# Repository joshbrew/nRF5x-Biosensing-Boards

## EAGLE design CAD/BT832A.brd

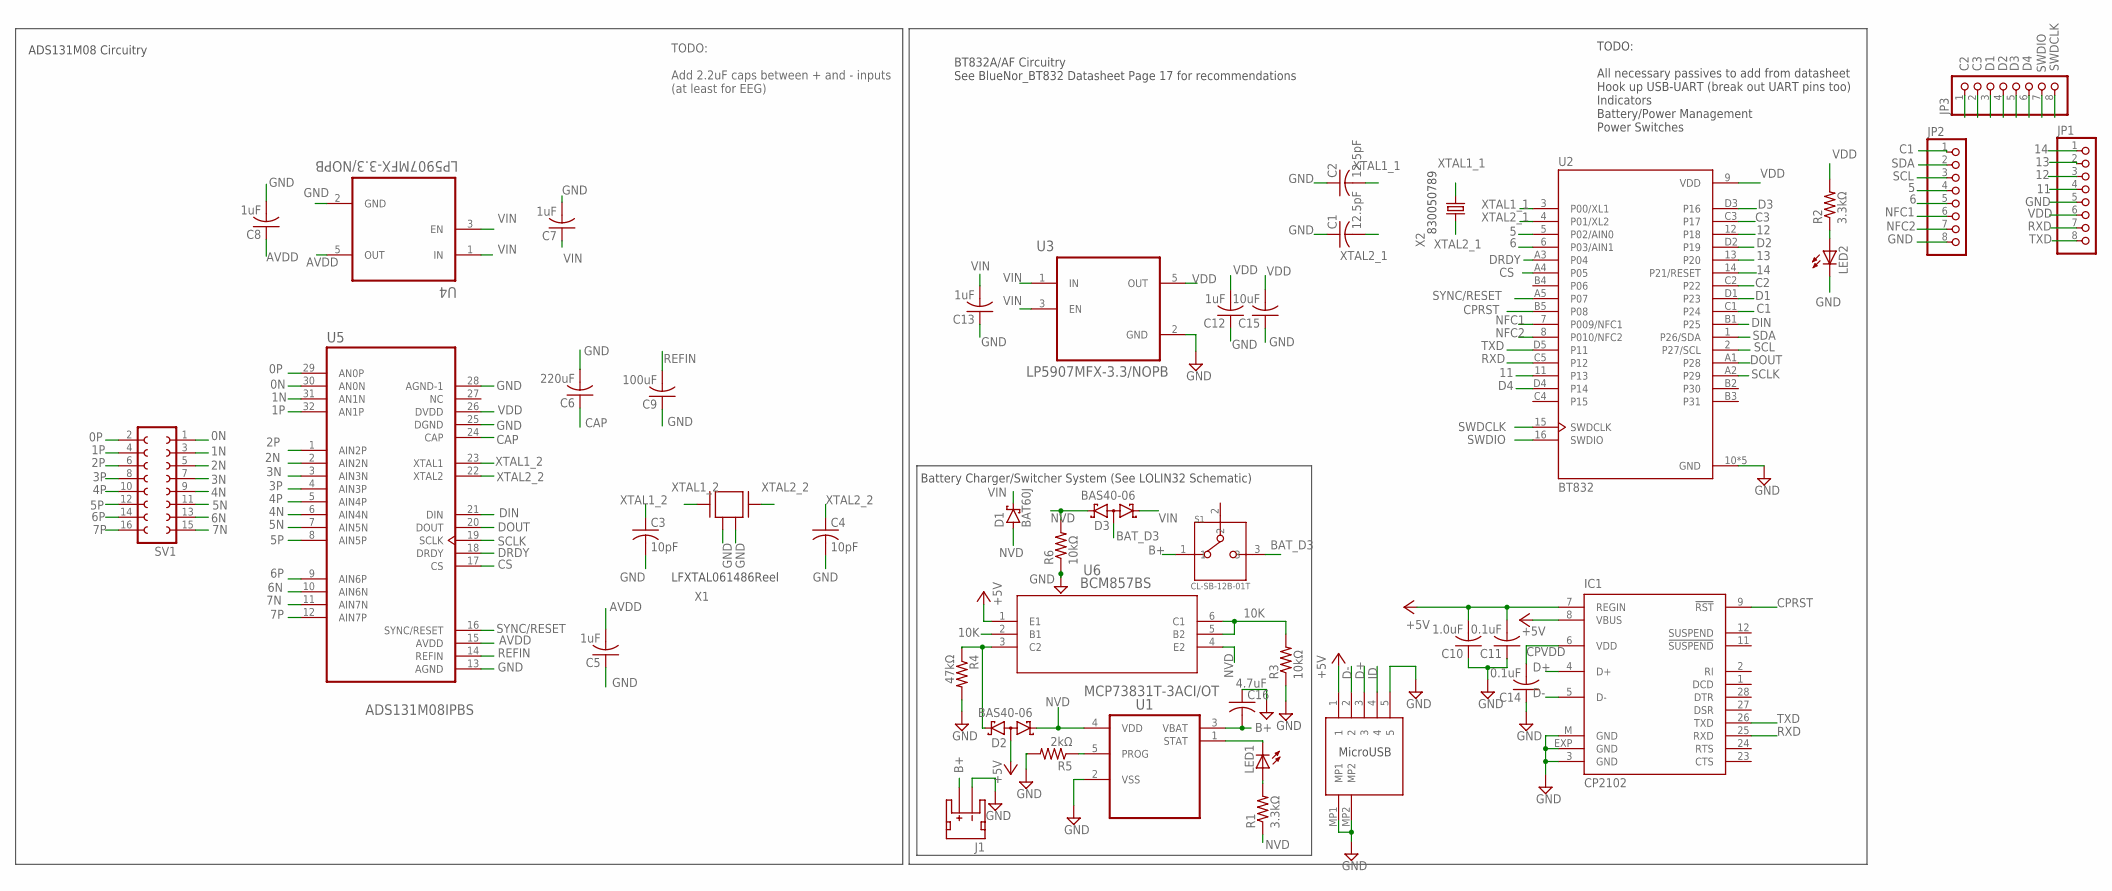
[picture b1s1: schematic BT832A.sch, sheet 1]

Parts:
C1, C2: 12.5pF; C0402
C3, C4: 10pF; C0402
C5, C7, C8, C12, C13: 1uF; C0402
C6: 220uF; C0402
C9: 100uF; C0402
C10: 1.0uF; C0402
C11, C14: 0.1uF; C0402
C15: 10uF; C0402
C16: 4.7uF; C0402
D1: BAT60J; SOD323_ST
D2, D3: BAS40-06; SOT23
IC1: CP2102; MLP28
J1: JST_2MM_MALE; JST-2-SMD
JP1, JP2, JP3: PINHD-1X8CLEANBIG; 1X08-CLEANBIG
LED1, LED2: LEDCHIP-LED0603; CHIP-LED0603
R1, R2: 3.3kΩ; R0402
R3, R6: 10kΩ; R0402
R4: 47kΩ; R0402
R5: 2kΩ; R0402
S1: CL-SB-12B-01T; CL-SB-12B
SV1: FE08-2
U1: MCP73831T-3ACI/OT; SOT95P270X145-5N
U2: BT832; BLEMODULE_BT832
U3, U4: LP5907MFX-3.3/NOPB; SOT95P280X145-5N
U5: ADS131M08IPBS; QFP50P700X700X120-32N
U6: BCM857BS; SOT363_NEX
U$1: DX4R005JJ2R1800
X1: ABM3B-8.000MHZ-B2-T
X2: FC-12M

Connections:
0N: SV1.1, U5.30 (AN0N)
0P: SV1.2, U5.29 (AN0P)
1N: SV1.3, U5.31 (AN1N)
1P: SV1.4, U5.32 (AN1P)
2N: SV1.5, U5.2 (AIN2N)
2P: SV1.6, U5.1 (AIN2P)
3N: SV1.7, U5.3 (AIN3N)
3P: SV1.8, U5.4 (AIN3P)
4N: SV1.9, U5.6 (AIN4N)
4P: SV1.10, U5.5 (AIN4P)
5: JP2.4, U2.5 (P02/AIN0)
5N: SV1.11, U5.7 (AIN5N)
5P: SV1.12, U5.8 (AIN5P)
6: JP2.5, U2.6 (P03/AIN1)
6N: SV1.13, U5.10 (AIN6N)
6P: SV1.14, U5.9 (AIN6P)
7N: SV1.15, U5.11 (AIN7N)
7P: SV1.16, U5.12 (AIN7P)
10K: R3.2, U6.2 (B1), U6.5 (B2), U6.6 (C1)
11: JP1.4, U2.11 (P13)
12: JP1.3, U2.12 (P18)
13: JP1.2, U2.13 (P20)
14: JP1.1, U2.14 (P21/RESET)
+5V: C10.2, C11.2, D2.3 (AA), IC1.7 (REGIN), IC1.8 (VBUS), U6.1 (E1), U$1.1; also elsewhere on the board
AVDD: C5.2, C8.1, U4.5 (OUT), U5.15 (AVDD)
B+: C16.2, J1.2 (+), S1.1, U1.3 (VBAT)
BAT_D3: D3.3 (AA), S1.3
C1: JP2.1, U2.C1 (P24)
C2: JP3.1, U2.C2 (P22)
C3: JP3.2, U2.C3 (P17)
CAP: C6.1, U5.24 (CAP)
CPRST: IC1.9 (!RST), U2.B5 (P08); also elsewhere on the board
CS: U2.A4 (P05), U5.17 (CS)
D1: JP3.3, U2.D1 (P23)
D2: JP3.4, U2.D2 (P19)
D3: JP3.5, U2.D3 (P16)
D4: JP3.6, U2.D4 (P14)
D+: IC1.4 (D+), U$1.3; also elsewhere on the board
D-: IC1.5 (D-), U$1.2; also elsewhere on the board
DIN: U2.B1 (P25), U5.21 (DIN)
DOUT: U2.A1 (P28), U5.20 (DOUT)
DRDY: U2.A3 (P04), U5.18 (DRDY)
GND: C1.1, C2.1, C3.2, C4.2, C5.1, C6.2, C7.2, C8.2, C9.1, C10.1, C11.1, C12.1, C13.1, C14.1, C15.1, C16.1, IC1.3 (GND), IC1.EXP (GND), IC1.M (GND), J1.1 (-), JP1.5, JP2.8, LED2.C, R3.1, R4.2, R5.2, R6.1, U1.2 (VSS), U2.10 (GND), U2.A0 (GND), U2.B0 (GND), U2.C0 (GND), U2.D0 (GND), U3.2 (GND), U4.2 (GND), U5.13 (AGND), U5.25 (DGND), U5.28 (AGND-1), U$1.5, U$1.MP1, U$1.MP2, X1.2, X1.4; also elsewhere on the board
ID: U$1.4
unnamed: LED2.A, R2.1
unnamed: R5.1, U1.5 (PROG)
unnamed: LED1.A, R1.2
unnamed: D2.2 (K2), R4.1, U6.3 (C2)
unnamed: LED1.C, U1.1 (STAT)
NFC1: JP2.6, U2.7 (P009/NFC1)
NFC2: JP2.7, U2.8 (P010/NFC2)
NVD: D1.A, D2.1 (K1), D3.2 (K2), R1.1, R6.2, U1.4 (VDD), U6.4 (E2); also elsewhere on the board
unnamed: C14.2, IC1.6 (VDD)
REFIN: C9.2, U5.14 (REFIN)
RXD: IC1.25 (RXD), JP1.7, U2.C5 (P12); also elsewhere on the board
SCL: JP2.3, U2.2 (P27/SCL)
SCLK: U2.A2 (P29), U5.19 (SCLK)
SDA: JP2.2, U2.1 (P26/SDA)
SWDCLK: JP3.8, U2.15 (SWDCLK)
SWDIO: JP3.7, U2.16 (SWDIO)
SYNC/RESET: U2.A5 (P07), U5.16 (SYNC/RESET)
TXD: IC1.26 (TXD), JP1.8, U2.D5 (P11); also elsewhere on the board
VDD: C12.2, C15.2, JP1.6, R2.2, U2.9 (VDD), U3.5 (OUT), U5.26 (DVDD)
VIN: C7.1, C13.2, D1.C, D3.1 (K1), U3.1 (IN), U3.3 (EN), U4.1 (IN), U4.3 (EN)
XTAL1_1: C2.2, U2.3 (P00/XL1), X2.2
XTAL1_2: C3.1, U5.23 (XTAL1), X1.1
XTAL2_1: C1.2, U2.4 (P01/XL2), X2.1
XTAL2_2: C4.1, U5.22 (XTAL2), X1.3

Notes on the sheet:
LFXTAL061486Reel
830050789
MicroUSB
TODO: Add 2.2uF caps between + and - inputs (at least for EEG)
Battery Charger/Switcher System (See LOLIN32 Schematic)
ADS131M08 Circuitry
BT832A/AF Circuitry See BlueNor_BT832 Datasheet Page 17 for recommendations
TODO: All necessary passives to add from datasheet Hook up USB-UART (break out UART pins too) Indicators Battery/Power Management Power Switches

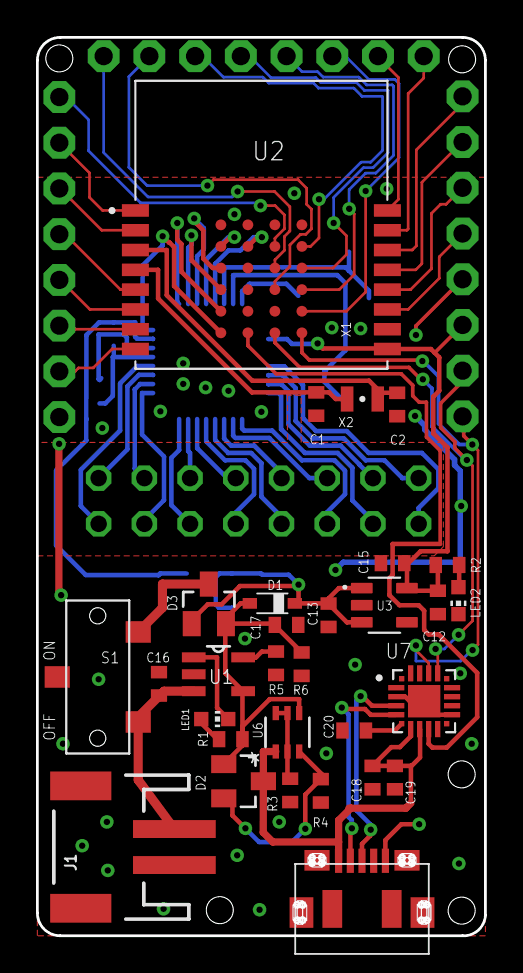
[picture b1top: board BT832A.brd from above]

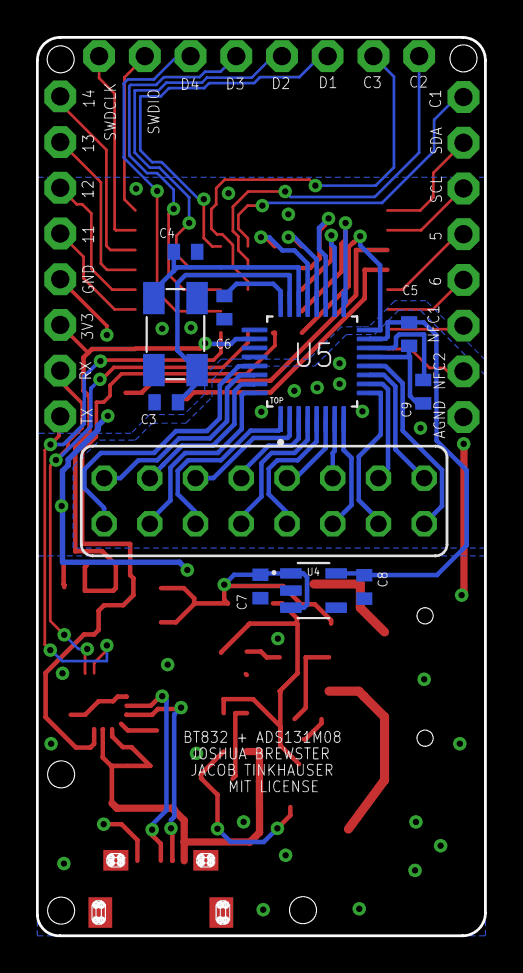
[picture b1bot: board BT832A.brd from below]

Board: 2 copper layers, 24.9 x 49.9 mm, 44 parts (11 on the bottom side), 67 nets.

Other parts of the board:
C17: 4.7uF; C0402
C18: 1.0uF; C0402
C19, C20: 0.1uF; C0402
U7: CP2102N-A02-GQFN20R; SILABS_CP2102N-A02-GQFN20R

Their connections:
+5V: C18.2, C19.2, U7.7, U7.8; also elsewhere on the board
CPRST: U7.9; also elsewhere on the board
CPVDD: C20.2, U7.6
D+: U7.4; also elsewhere on the board
D-: U7.5; also elsewhere on the board
GND: C17.1, C18.1, C19.1, C20.1, U7.3, U7.12, U7.21; also elsewhere on the board
NVD: C17.2; also elsewhere on the board
RXD: U7.17; also elsewhere on the board
TXD: U7.18; also elsewhere on the board

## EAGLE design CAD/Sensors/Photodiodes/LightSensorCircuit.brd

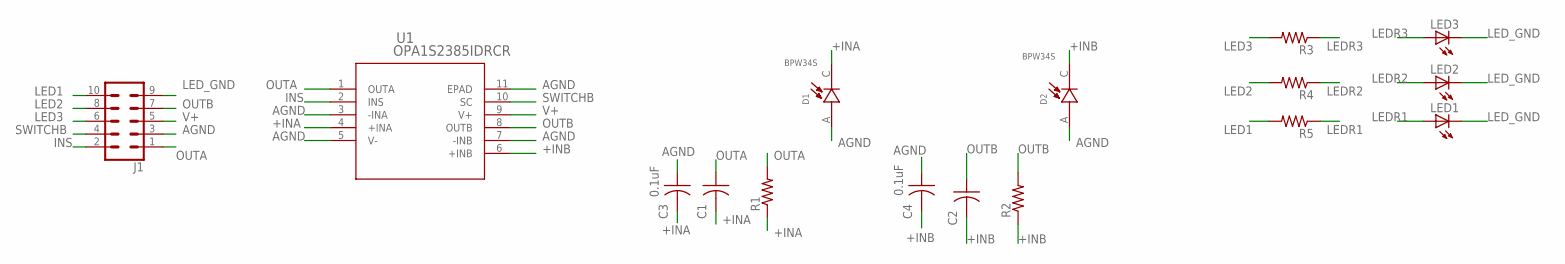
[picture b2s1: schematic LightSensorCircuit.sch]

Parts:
C1, C2: C-US025-025X050; C025-025X050
C3, C4: 0.1uF; C025-025X050
D1, D2: BPW34S; DIO_BPW34S
J1: CONN_05X2NO_SILK; 2X5_NOSILK
LED1, LED2, LED3: LEDCHIPLED_1206; CHIPLED_1206
R1, R2, R3, R4, R5: R-US_0204/5; 0204/5
U1: OPA1S2385IDRCR; DRC10_1P65X2P40_TEX

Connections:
+INA: C1.2, C3.2, D1.C, R1.1, U1.4 (+INA)
+INB: C2.2, C4.2, D2.C, R2.1, U1.6 (+INB)
AGND: C3.1, C4.1, D1.A, D2.A, J1.3, U1.3 (-INA), U1.5 (V-), U1.7 (-INB), U1.11 (EPAD)
INS: J1.2, U1.2 (INS)
LED1: J1.10, R5.2
LED2: J1.8, R4.2
LED3: J1.6, R3.2
LEDR1: LED1.A, R5.1
LEDR2: LED2.A, R4.1
LEDR3: LED3.A, R3.1
LED_GND: J1.9, LED1.C, LED2.C, LED3.C
OUTA: C1.1, J1.1, R1.2, U1.1 (OUTA)
OUTB: C2.1, J1.7, R2.2, U1.8 (OUTB)
SWITCHB: J1.4, U1.10 (SC)
V+: J1.5, U1.9 (V+)

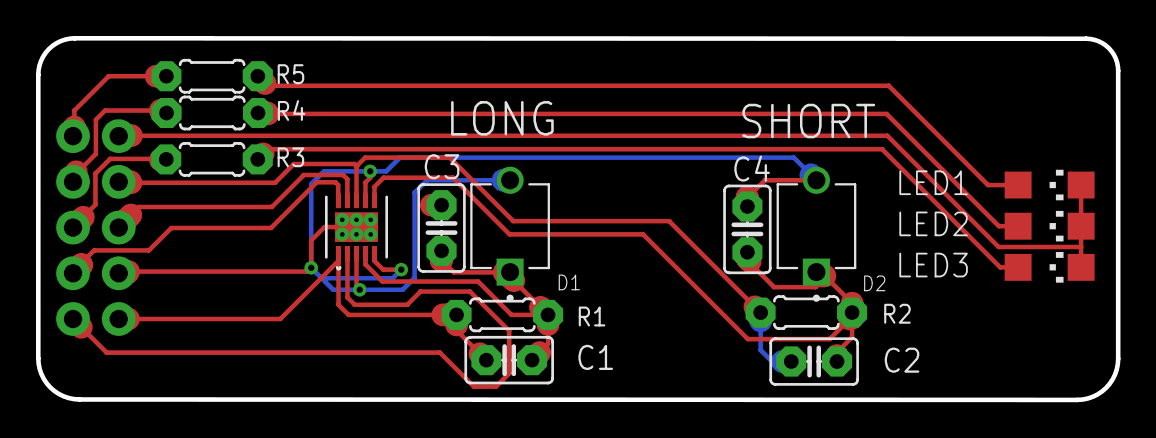
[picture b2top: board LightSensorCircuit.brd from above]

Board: 2 copper layers, 60.0 x 20.1 mm, 16 parts (0 on the bottom side), 15 nets.

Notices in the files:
CAD/BT832A.brd:
MIT LICENSE
CAD/Sensors/Photodiodes/LightSensorCircuit.brd:
AGPL v3 License
parts and their libraries:
SparkFun-Connectors: Licensing: Creative Commons ShareAlike 4.0 International - https://creativecommons.org/licenses/by-sa/4.0
COPYRIGHT: Copyright (C) 2016 Accelerated Designs. All rights reserved
COPYRIGHT: Copyright (C) 2022 Ultra Librarian. All rights reserved.
